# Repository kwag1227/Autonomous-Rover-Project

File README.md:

# Autonomous Rover Project

This repository contains all design files, software, and documentation for an all-terrain, six-legged rover capable of navigating rough terrain and collecting environmental samples. It is a personal robotics project focused on demonstrating skills in embedded systems, motor control, and computer vision.

## 🚀 Project Goals

- Navigate difficult terrain using a rocker-bogie suspension system
- Collect and store small samples (e.g., rocks or soil)
- Avoid untraversable obstacles using sensors
- Showcase design and control of a multi-motor robotic system
- Build a custom PCB
- Implement ROS2 and Gazebo Simulation

## 📁 Repository Structure

- /code                       Microcontroller firmware and Raspberry Pi software  
- /mechanical design          CAD files & mechanical designs
- /electrical schematics      PCB schematics & electrical diagrams
- /vision                     Computer vision and object detection scripts  
- /docs                       Design notes and planning documents 
- /tests                      Testing scripts and logs  
- /media                      Images or videos of the rover in progress
- /references                 Reference images that I gathered from online
- /archives                   Outdated documents/files that are no longer in use
- README.md                   Project overview and documentation  

## 🧰 Technologies Used

- Raspberry Pi 4 (with OpenCV for computer vision)
- Raspberry Pi Pico
- Python Programming Language and ROS
- Rocker-Bogie Suspension System
- Camera Module
- Sensors (IMU, GPS, Encoders, Magnetometer)
- Custom PCB

## 🛠️ Current Progress

- [x] Preliminary Research
- [x] Conceptual Design
- [x] Power Distribution Design
- [x] Control/Communication Design
- [x] Master Electrical Schematic Design
- [x] PCB Design
- [x] CAD Design
- [x] Finalized BOM
- [x] Mechanical Assembly
- [ ] Electrical Assembly
- [ ] Basic Drive Logic
- [ ] Autonomy Logic
- [ ] Articulated Arm Design
- [ ] Articulation Logic 

## 📷 Media

*Add photos or videos here later*

## 🔒 Status

This is a personal project still under development

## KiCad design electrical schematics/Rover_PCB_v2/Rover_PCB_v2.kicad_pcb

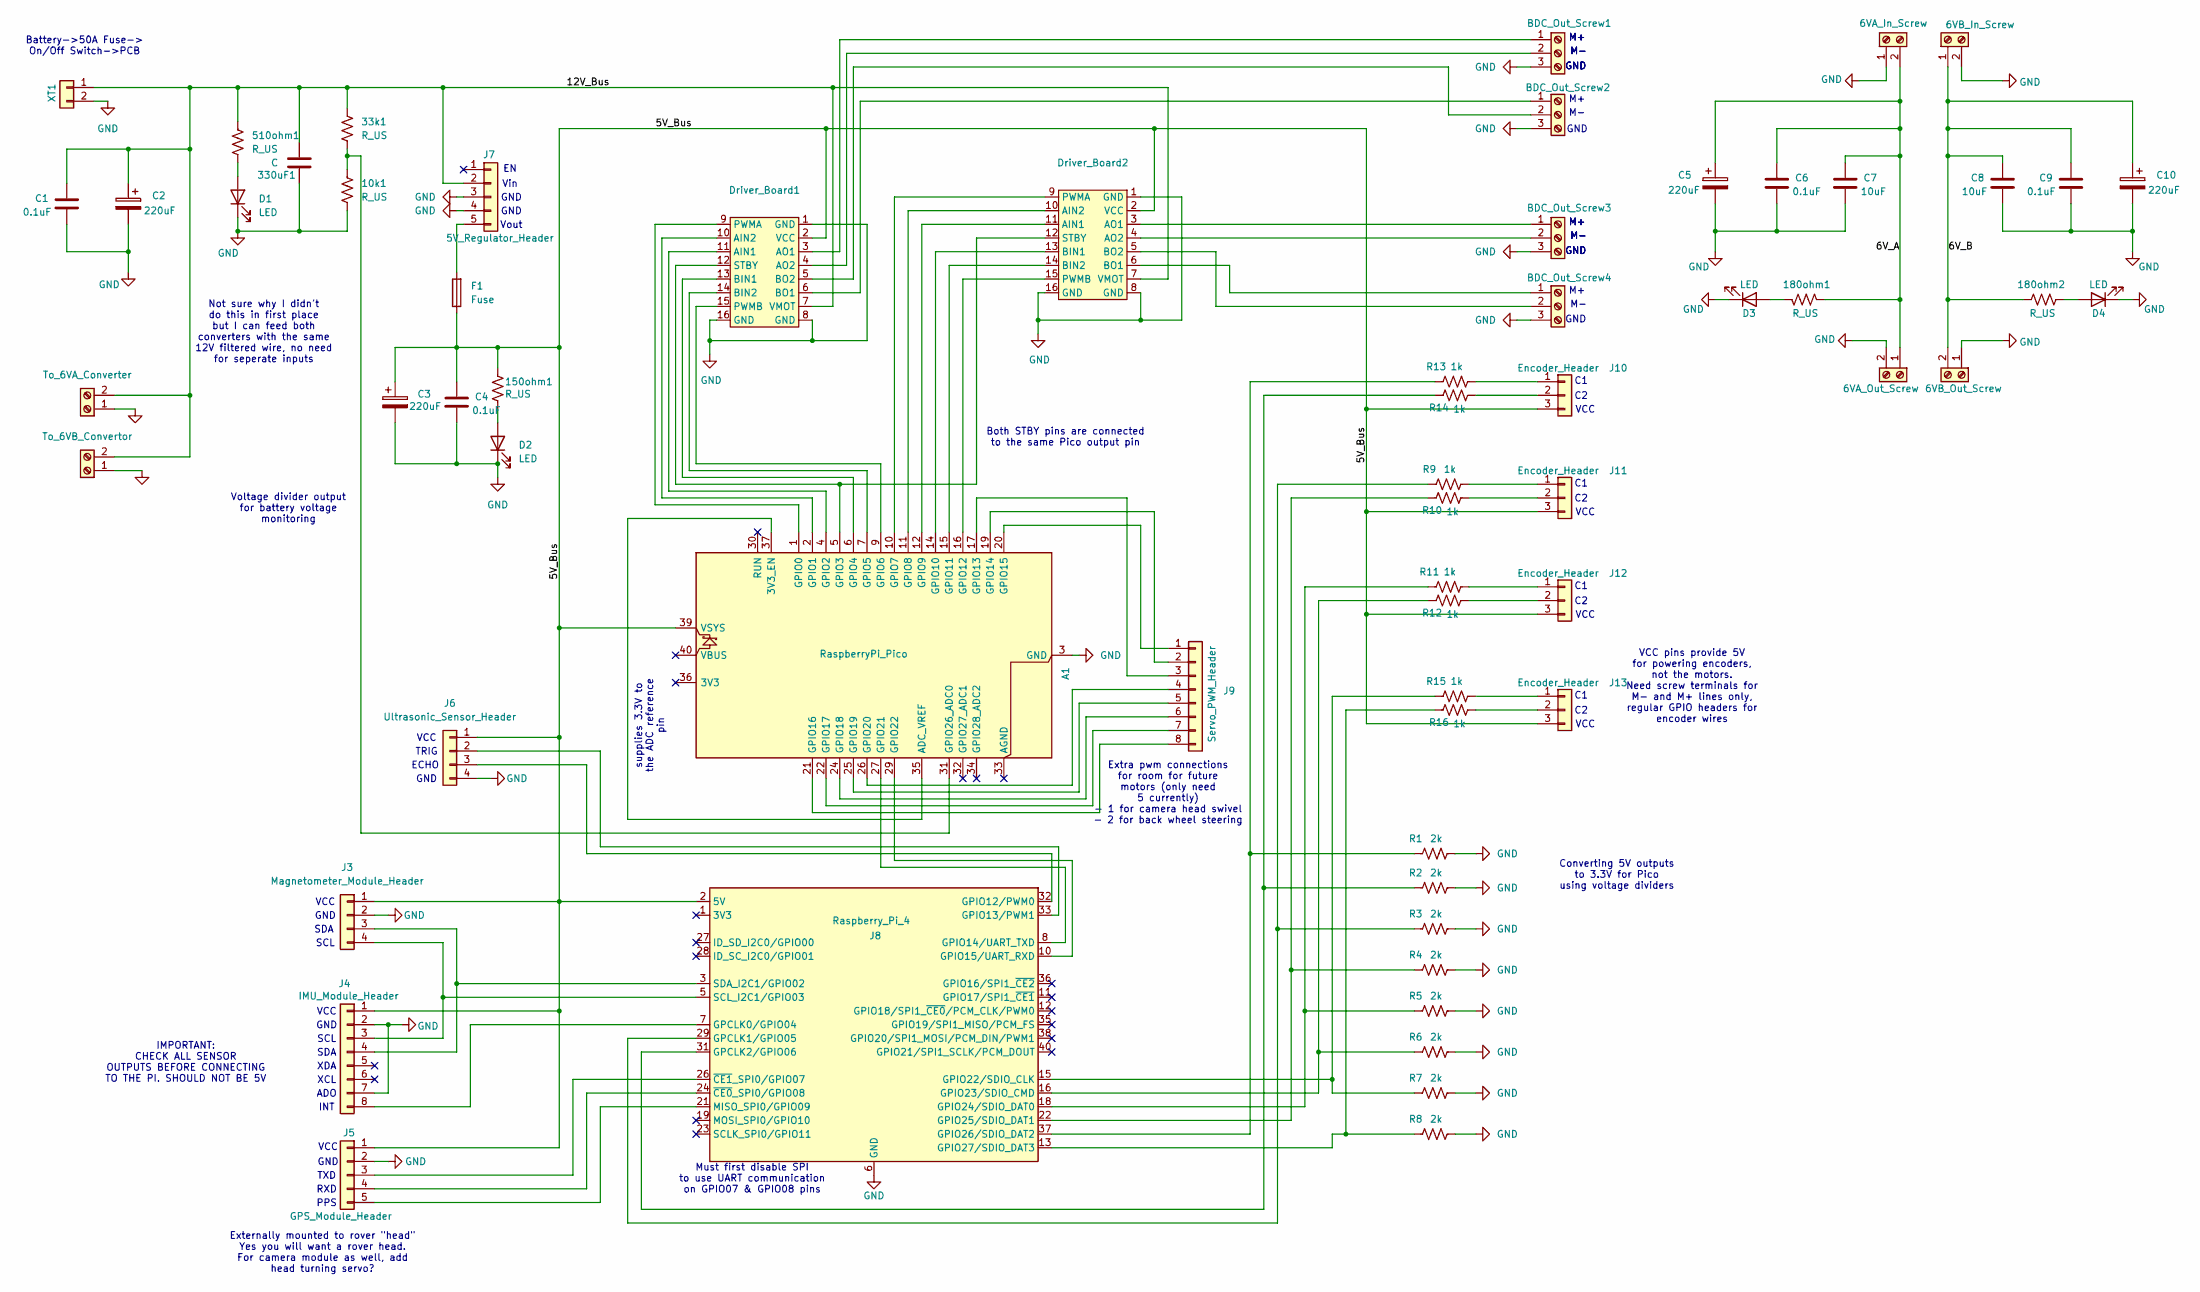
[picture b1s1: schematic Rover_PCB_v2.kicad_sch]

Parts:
10k1, 33k1, 150ohm1, 180ohm1, 180ohm2, 510ohm1: R_US; R_Axial_DIN0207_L6.3mm_D2.5mm_P7.62mm_Horizontal
330uF1: C; CP_Radial_D4.0mm_P2.00mm
A1: RaspberryPi_Pico; RaspberryPi_Pico_Common_Unspecified
BDC_Out_Screw1, BDC_Out_Screw2, BDC_Out_Screw3, BDC_Out_Screw4: BDC_Motor_Screw_Terminal; 01x03_Screw_Terminal
C1, C4, C6, C9: 0.1uF; CP_Radial_D4.0mm_P2.00mm
C2, C3, C5, C10: 220uF; CP_Radial_D6.3mm_P2.50mm
C7, C8: 10uF; CP_Radial_D4.0mm_P2.00mm
D1, D2, D3, D4: LED; LED_D3.0mm
Driver_Board1, Driver_Board2: Motor Driver Board
F1: Fuse; Fuse_TH_5A
J1: To_6VA_Converter; 12AWG Screw Terminal
J2: To_6VB_Convertor; 12AWG Screw Terminal
J3: Magnetometer_Module_Header; PinHeader_1x04_P2.54mm_Vertical
J4: IMU_Module_Header; PinHeader_1x08_P2.54mm_Vertical
J5: GPS_Module_Header; PinHeader_1x05_P2.54mm_Vertical
J6: Ultrasonic_Sensor_Header; PinHeader_1x04_P2.54mm_Vertical
J7: 5V_Regulator_Header; PinHeader_1x05_P2.54mm_Vertical
J8: Raspberry_Pi_4; SULLINS_PPTC202LFBN-RC
J9: Servo_PWM_Header; PinHeader_1x08_P2.54mm_Vertical
J10, J11, J12, J13: Encoder_Header; PinHeader_1x03_P2.54mm_Vertical
J14: 6VA_In_Screw; 12AWG Screw Terminal
J15: 6VA_Out_Screw; 12AWG Screw Terminal
J16: 6VB_In_Screw; 12AWG Screw Terminal
J17: 6VB_Out_Screw; 12AWG Screw Terminal
R1, R2, R3, R4, R5, R6, R7, R8: 2k; R_Axial_DIN0207_L6.3mm_D2.5mm_P7.62mm_Horizontal
R9, R10, R11, R12, R13, R14, R15, R16: 1k; R_Axial_DIN0207_L6.3mm_D2.5mm_P7.62mm_Horizontal
XT1: XT60_Port; AMASS_XT60-F_1x02_P7.20mm_Vertical

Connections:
/5V_Bus: 150ohm1.1, A1.39 (VSYS), C3.1, C4.1, Driver_Board1.2 (VCC), Driver_Board2.2 (VCC), F1.1, J3.1 (VCC), J4.1, J5.1 (VCC), J6.1 (VCC), J8.2 (5V), J8.4 (5V), J10.3 (VCC), J11.3 (VCC), J12.3 (VCC), J13.3 (VCC)
/6V_A: 180ohm1.1, C5.1, C6.1, C7.1, J14.2, J15.1
/6V_B: 180ohm2.1, C8.1, C9.1, C10.1, J16.1, J17.2
/12V_Bus: 33k1.2, 330uF1.1, 510ohm1.1, C1.1, C2.1, Driver_Board1.7 (VMOT), Driver_Board2.7 (VMOT), J1.2, J2.2, J7.2 (Vin), XT1.1 (12V_raw); also elsewhere on the board
GND: 10k1.2, 330uF1.2, A1.3 (GND), A1.8 (GND), A1.13 (GND), A1.18 (GND), A1.23 (GND), A1.28 (GND), A1.38 (GND), BDC_Out_Screw1.3 (GND), BDC_Out_Screw2.3 (GND), BDC_Out_Screw3.3 (GND), BDC_Out_Screw4.3 (GND), C1.2, C2.2, C3.2, C4.2, C5.2, C6.2, C7.2, C8.2, C9.2, C10.2, D1.2 (K), D2.2 (K), D3.2 (K), D4.2 (K), Driver_Board1.1 (GND), Driver_Board1.8 (GND), Driver_Board1.16 (GND), Driver_Board2.1 (GND), Driver_Board2.8 (GND), Driver_Board2.16 (GND), J1.1, J2.1, J3.2 (GND), J4.2, J4.7, J5.2 (GND), J6.4 (GND), J7.3 (GND), J7.4 (GND), J8.6 (GND), J8.9 (GND), J8.14 (GND), J8.20 (GND), J8.25 (GND), J8.30 (GND), J8.34 (GND), J8.39 (GND), J14.1, J15.2, J16.2, J17.1, R1.2, R2.2, R3.2, R4.2, R5.2, R6.2, R7.2, R8.2, XT1.2 (GND); also elsewhere on the board
unnamed: A1.35 (ADC_VREF), A1.37 (3V3_EN)
unnamed: A1.1 (GPIO0), Driver_Board1.9 (PWMA)
unnamed: A1.2 (GPIO1), Driver_Board1.10 (AIN2)
unnamed: A1.4 (GPIO2), Driver_Board1.11 (AIN1)
unnamed: A1.5 (GPIO3), Driver_Board1.12 (STBY), Driver_Board2.12 (STBY)
unnamed: A1.6 (GPIO4), Driver_Board1.13 (BIN1)
unnamed: A1.7 (GPIO5), Driver_Board1.14 (BIN2)
unnamed: A1.9 (GPIO6), Driver_Board1.15 (PWMB)
unnamed: A1.10 (GPIO7), Driver_Board2.9 (PWMA)
unnamed: A1.11 (GPIO8), Driver_Board2.10 (AIN2)
unnamed: A1.12 (GPIO9), Driver_Board2.11 (AIN1)
unnamed: A1.14 (GPIO10), Driver_Board2.13 (BIN1)
unnamed: A1.15 (GPIO11), Driver_Board2.14 (BIN2)
unnamed: A1.16 (GPIO12), Driver_Board2.15 (PWMB)
unnamed: A1.17 (GPIO13), J9.3
unnamed: A1.19 (GPIO14), J9.2
unnamed: A1.20 (GPIO15), J9.1
unnamed: A1.21 (GPIO16), J9.8
unnamed: A1.22 (GPIO17), J9.7
unnamed: A1.24 (GPIO18), J9.6
unnamed: A1.25 (GPIO19), J9.5
unnamed: A1.26 (GPIO20), J9.4
unnamed: A1.27 (GPIO21), J8.8 (GPIO14/UART_TXD)
unnamed: A1.29 (GPIO22), J8.10 (GPIO15/UART_RXD)
unnamed: 10k1.1, 33k1.1, A1.31 (GPIO26_ADC0)
unnamed 30: BDC_Out_Screw1.1 (M+), Driver_Board1.3 (AO1); also elsewhere on the board
unnamed 31: BDC_Out_Screw1.2 (M-), Driver_Board1.4 (AO2); also elsewhere on the board
unnamed: BDC_Out_Screw2.1 (M+), Driver_Board1.6 (BO1)
unnamed: BDC_Out_Screw2.2 (M-), Driver_Board1.5 (BO2)
unnamed: BDC_Out_Screw3.1 (M+), Driver_Board2.3 (AO1)
unnamed: BDC_Out_Screw3.2 (M-), Driver_Board2.4 (AO2)
unnamed: BDC_Out_Screw4.1 (M+), Driver_Board2.6 (BO1)
unnamed: BDC_Out_Screw4.2 (M-), Driver_Board2.5 (BO2)
unnamed: 510ohm1.2, D1.1 (A)
unnamed: 150ohm1.2, D2.1 (A)
unnamed: 180ohm1.2, D3.1 (A)
unnamed: 180ohm2.2, D4.1 (A)
unnamed: J3.4 (SCL), J4.3, J8.5 (SCL_I2C1/GPIO03)
unnamed: J3.3 (SDA), J4.4, J8.3 (SDA_I2C1/GPIO02)
unnamed: J4.8, J8.7 (GPCLK0/GPIO04)
unnamed: J5.5 (PPS), J8.21 (MISO_SPI0/GPIO09)
unnamed: J5.4 (RXD), J8.24 (~CE0_SPI0/GPIO08)
unnamed: J5.3 (TXD), J8.26 (~CE1_SPI0/GPIO07)
unnamed: J6.3 (Echo), J8.32 (GPIO12/PWM0)
unnamed: J6.2 (Trig), J8.33 (GPIO13/PWM1)
unnamed: F1.2, J7.5 (Vout)
unnamed: J8.29 (GPCLK1/GPIO05), R3.1, R9.1
unnamed: J8.31 (GPCLK2/GPIO06), R2.1, R14.1
unnamed: J8.15 (GPIO22/SDIO_CLK), R7.1, R15.1
unnamed: J8.16 (GPIO23/SDIO_CMD), R6.1, R12.1
unnamed: J8.18 (GPIO24/SDIO_DAT0), R5.1, R11.1
unnamed: J8.22 (GPIO25/SDIO_DAT1), R4.1, R10.1
unnamed: J8.37 (GPIO26/SDIO_DAT2), R1.1, R13.1
unnamed: J8.13 (GPIO27/SDIO_DAT3), R8.1, R16.1
unnamed: J10.1 (C1), R13.2
unnamed: J10.2 (C2), R14.2
unnamed: J11.1 (C1), R9.2
unnamed: J11.2 (C2), R10.2
unnamed: J12.1 (C1), R11.2
unnamed: J12.2 (C2), R12.2
unnamed: J13.1 (C1), R15.2
unnamed: J13.2 (C2), R16.2

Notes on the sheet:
GND
INT
Externally mounted to rover "head" Yes you will want a rover head. For camera module as well, add head turning servo?
GND
TRIG
VCC
Vin
SDA
SCL
supplies 3.3V to the ADC reference pin
TXD
Voltage divider output for battery voltage monitoring
XCL
Battery->50A Fuse-> On/Off Switch->PCB
IMPORTANT: CHECK ALL SENSOR OUTPUTS BEFORE CONNECTING TO THE PI. SHOULD NOT BE 5V
RXD
VCC pins provide 5V for powering encoders, not the motors. Need screw terminals for M- and M+ lines only, regular GPIO headers for encoder wires
Vout
ECHO
PPS
Both STBY pins are connected to the same Pico output pin
Not sure why I didn't do this in first place but I can feed both converters with the same 12V filtered wire, no need for seperate inputs
XDA
Must first disable SPI to use UART communication on GPIO07 & GPIO08 pins
Extra pwm connections for room for future motors (only need 5 currently) - 1 for camera head swivel - 2 for back wheel steering
ADO
Converting 5V outputs to 3.3V for Pico using voltage dividers

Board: 2 copper layers, 63 parts (0 on the bottom side), 67 nets, no tracks yet.

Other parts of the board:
BDC_Out_Screw: BDC_Motor_Screw_Terminal; 01x03_Screw_Terminal
XT60: XT60_Port; AMASS_XT60-F_1x02_P7.20mm_Vertical

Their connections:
/12V_Bus: XT60.1 (12V_raw); also elsewhere on the board
GND: BDC_Out_Screw.3 (GND), XT60.2 (GND); also elsewhere on the board
unnamed 30: BDC_Out_Screw.1 (M+); also elsewhere on the board
unnamed 31: BDC_Out_Screw.2 (M-); also elsewhere on the board

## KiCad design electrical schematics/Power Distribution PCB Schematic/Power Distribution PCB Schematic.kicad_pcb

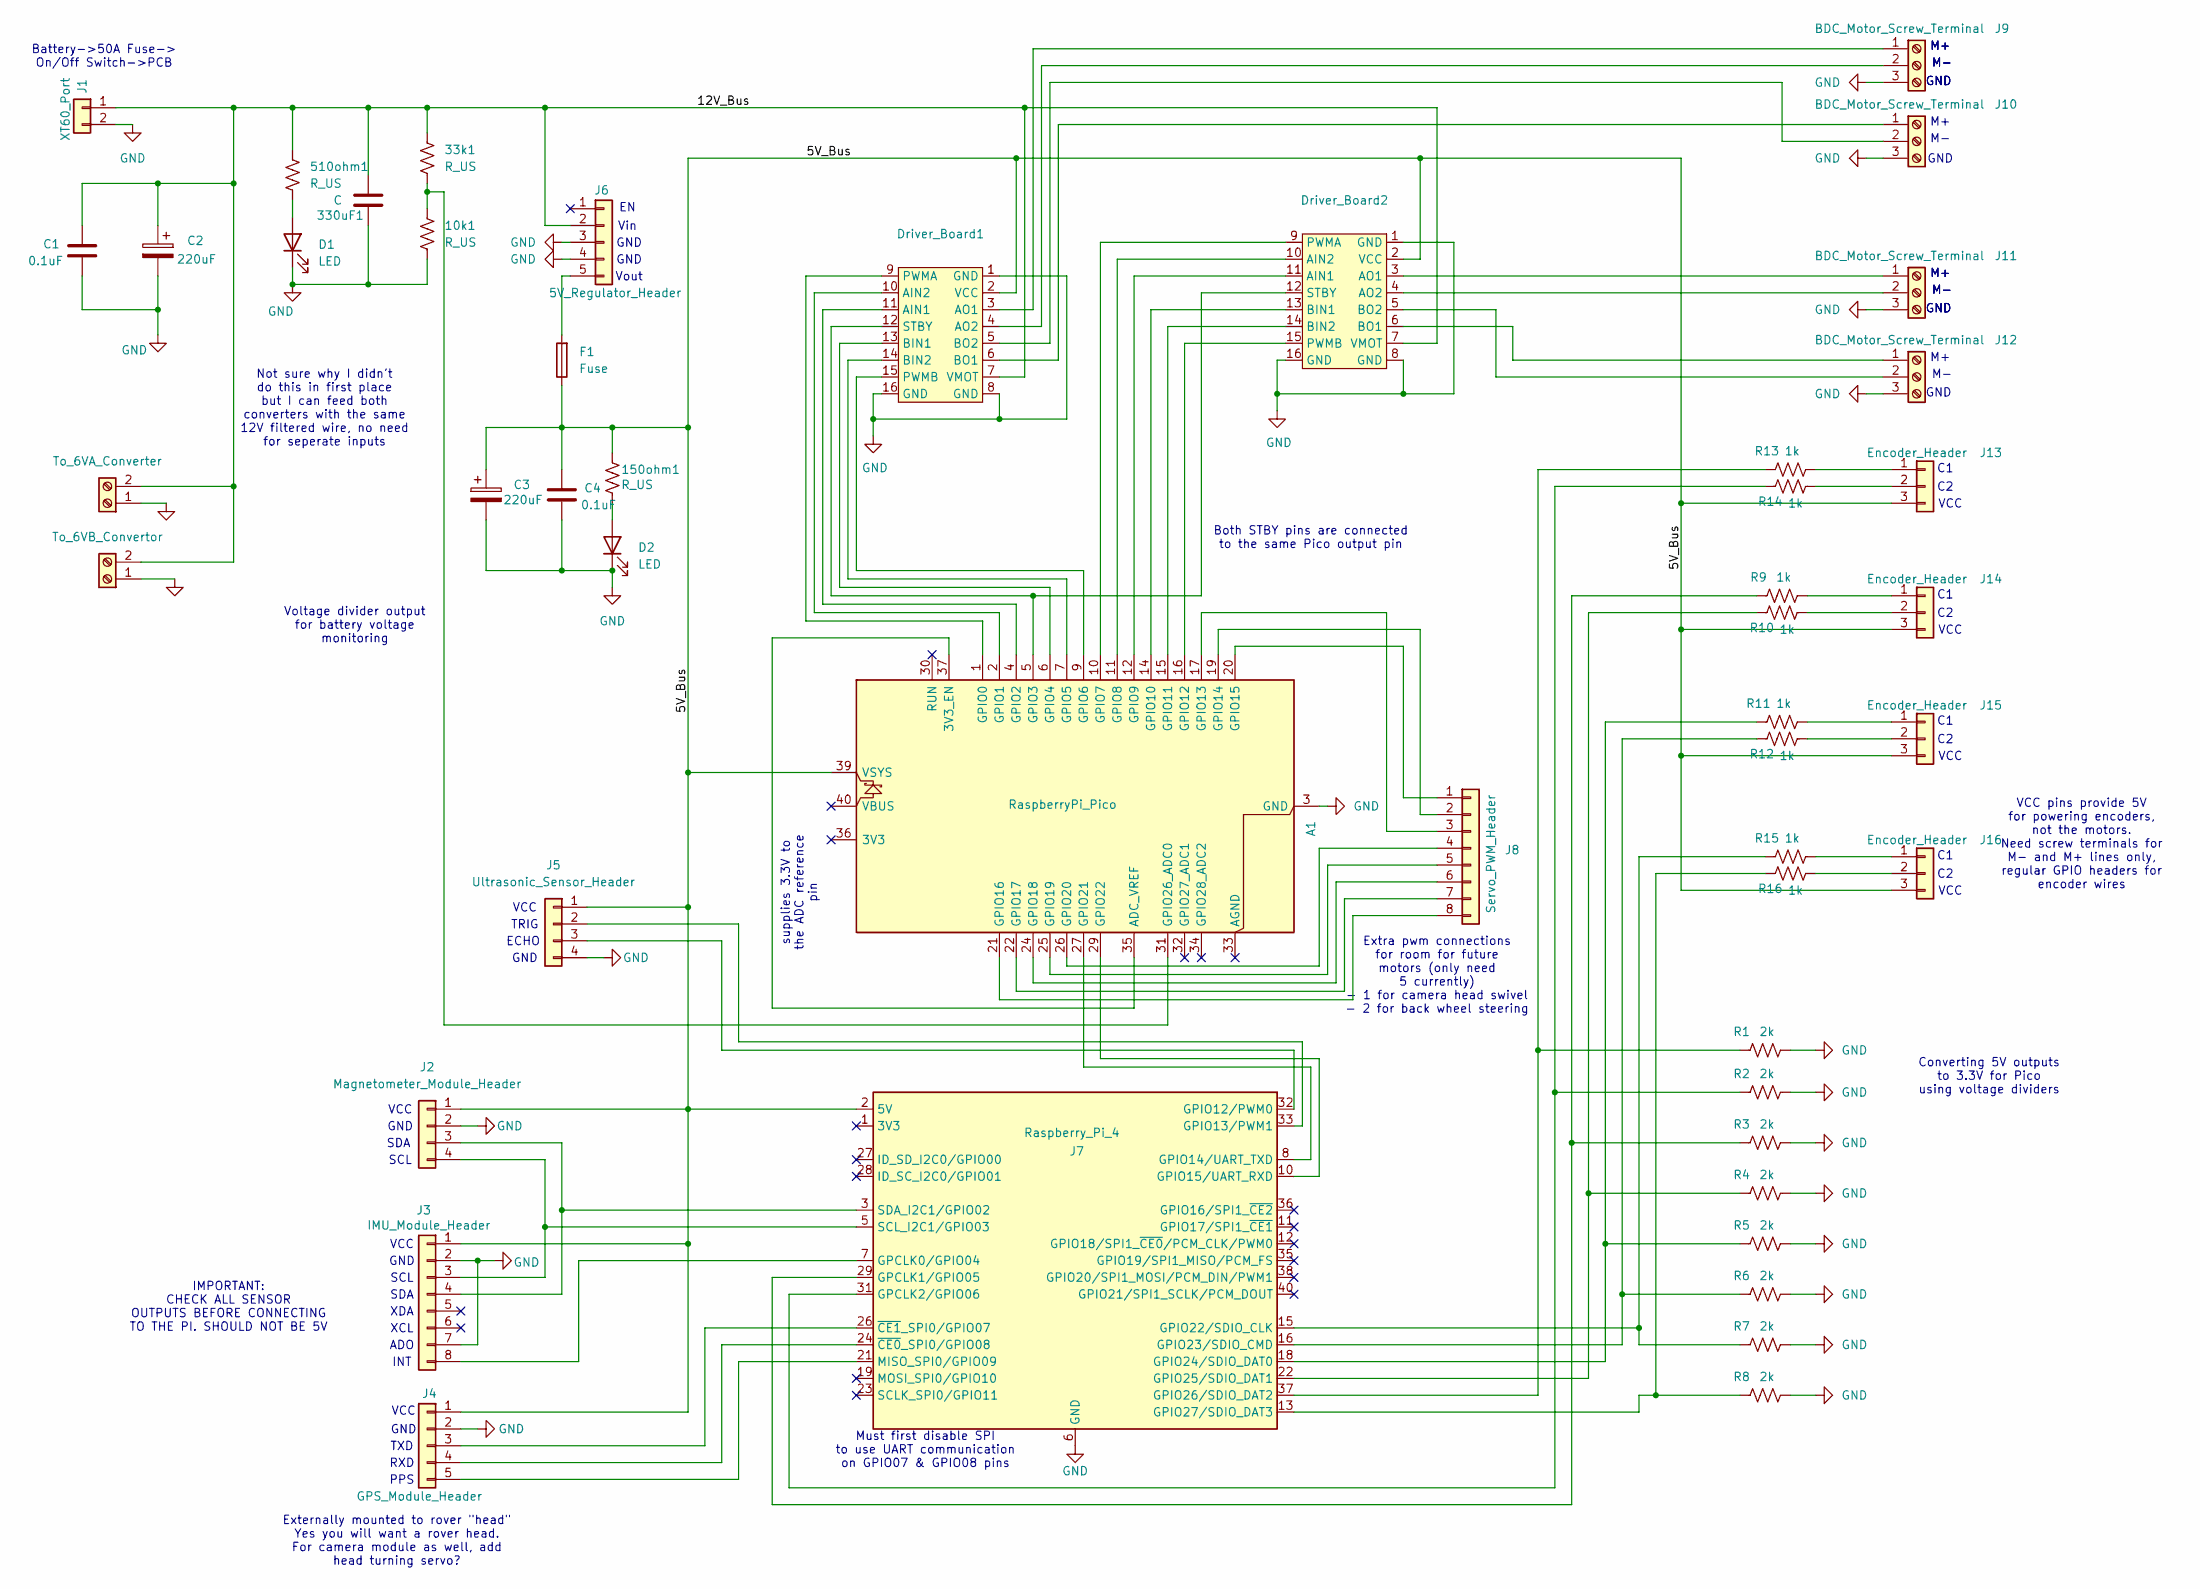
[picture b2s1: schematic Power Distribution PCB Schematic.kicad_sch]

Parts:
10k1, 33k1, 150ohm1, 510ohm1: R_US; R_Axial_DIN0207_L6.3mm_D2.5mm_P7.62mm_Horizontal
330uF1: C; Ceramic Cap
A1: RaspberryPi_Pico; RaspberryPi_Pico_Common_Unspecified
C1, C4: 0.1uF; Ceramic Cap
C2, C3: 220uF; CP_Radial_D6.3mm_P2.50mm
D1, D2: LED; LED_D3.0mm
Driver_Board1, Driver_Board2: Motor Driver Board
F1: Fuse; Fuse_TH_5A
J1: XT60_Port; AMASS_XT60-F_1x02_P7.20mm_Vertical
J2: Magnetometer_Module_Header; PinHeader_1x04_P2.54mm_Vertical
J3: IMU_Module_Header; PinHeader_1x08_P2.54mm_Vertical
J4: GPS_Module_Header; PinHeader_1x05_P2.54mm_Vertical
J5: Ultrasonic_Sensor_Header; PinHeader_1x04_P2.54mm_Vertical
J6: 5V_Regulator_Header; PinHeader_1x05_P2.54mm_Vertical
J7: Raspberry_Pi_4; SULLINS_PPTC202LFBN-RC
J8: Servo_PWM_Header; PinHeader_1x08_P2.54mm_Vertical
J9, J10, J11, J12: BDC_Motor_Screw_Terminal; 01x03_Screw_Terminal
J13, J14, J15, J16: Encoder_Header; PinHeader_1x03_P2.54mm_Vertical
R1, R2, R3, R4, R5, R6, R7, R8: 2k; R_Axial_DIN0207_L6.3mm_D2.5mm_P7.62mm_Horizontal
R9, R10, R11, R12, R13, R14, R15, R16: 1k; R_Axial_DIN0207_L6.3mm_D2.5mm_P7.62mm_Horizontal
To_6VA_Conv1: To_6VA_Converter; 12AWG Screw Terminal
To_6VB_Conv1: To_6VB_Convertor; 12AWG Screw Terminal

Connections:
/5V_Bus: 150ohm1.1, A1.39 (VSYS), C3.1, C4.1, Driver_Board1.2 (VCC), Driver_Board2.2 (VCC), F1.1, J2.1 (VCC), J3.1, J4.1 (VCC), J5.1 (VCC), J7.2 (5V), J7.4 (5V), J13.3 (VCC), J14.3 (VCC), J15.3 (VCC), J16.3 (VCC)
/12V_Bus: 33k1.2, 330uF1.1, 510ohm1.1, C1.1, C2.1, Driver_Board1.7 (VMOT), Driver_Board2.7 (VMOT), J1.1 (12V_raw), J6.2 (Vin), To_6VA_Conv1.2, To_6VB_Conv1.2
GND: 10k1.2, 330uF1.2, A1.3 (GND), A1.8 (GND), A1.13 (GND), A1.18 (GND), A1.23 (GND), A1.28 (GND), A1.38 (GND), C1.2, C2.2, C3.2, C4.2, D1.2 (K), D2.2 (K), Driver_Board1.1 (GND), Driver_Board1.8 (GND), Driver_Board1.16 (GND), Driver_Board2.1 (GND), Driver_Board2.8 (GND), Driver_Board2.16 (GND), J1.2 (GND), J2.2 (GND), J3.2, J3.7, J4.2 (GND), J5.4 (GND), J6.3 (GND), J6.4 (GND), J7.6 (GND), J7.9 (GND), J7.14 (GND), J7.20 (GND), J7.25 (GND), J7.30 (GND), J7.34 (GND), J7.39 (GND), J9.3 (GND), J10.3 (GND), J11.3 (GND), J12.3 (GND), R1.2, R2.2, R3.2, R4.2, R5.2, R6.2, R7.2, R8.2, To_6VA_Conv1.1, To_6VB_Conv1.1
unnamed: A1.35 (ADC_VREF), A1.37 (3V3_EN)
unnamed: A1.1 (GPIO0), Driver_Board1.9 (PWMA)
unnamed: A1.2 (GPIO1), Driver_Board1.10 (AIN2)
unnamed: A1.4 (GPIO2), Driver_Board1.11 (AIN1)
unnamed: A1.5 (GPIO3), Driver_Board1.12 (STBY), Driver_Board2.12 (STBY)
unnamed: A1.6 (GPIO4), Driver_Board1.13 (BIN1)
unnamed: A1.7 (GPIO5), Driver_Board1.14 (BIN2)
unnamed: A1.9 (GPIO6), Driver_Board1.15 (PWMB)
unnamed: A1.10 (GPIO7), Driver_Board2.9 (PWMA)
unnamed: A1.11 (GPIO8), Driver_Board2.10 (AIN2)
unnamed: A1.12 (GPIO9), Driver_Board2.11 (AIN1)
unnamed: A1.14 (GPIO10), Driver_Board2.13 (BIN1)
unnamed: A1.15 (GPIO11), Driver_Board2.14 (BIN2)
unnamed: A1.16 (GPIO12), Driver_Board2.15 (PWMB)
unnamed: A1.17 (GPIO13), J8.3
unnamed: A1.19 (GPIO14), J8.2
unnamed: A1.20 (GPIO15), J8.1
unnamed: A1.21 (GPIO16), J8.8
unnamed: A1.22 (GPIO17), J8.7
unnamed: A1.24 (GPIO18), J8.6
unnamed: A1.25 (GPIO19), J8.5
unnamed: A1.26 (GPIO20), J8.4
unnamed: A1.27 (GPIO21), J7.8 (GPIO14/UART_TXD)
unnamed: A1.29 (GPIO22), J7.10 (GPIO15/UART_RXD)
unnamed: 10k1.1, 33k1.1, A1.31 (GPIO26_ADC0)
unnamed: 510ohm1.2, D1.1 (A)
unnamed: 150ohm1.2, D2.1 (A)
unnamed: Driver_Board1.3 (AO1), J9.1 (M+)
unnamed: Driver_Board1.4 (AO2), J9.2 (M-)
unnamed: Driver_Board1.6 (BO1), J10.1 (M+)
unnamed: Driver_Board1.5 (BO2), J10.2 (M-)
unnamed: Driver_Board2.3 (AO1), J11.1 (M+)
unnamed: Driver_Board2.4 (AO2), J11.2 (M-)
unnamed: Driver_Board2.6 (BO1), J12.1 (M+)
unnamed: Driver_Board2.5 (BO2), J12.2 (M-)
unnamed: J2.4 (SCL), J3.3, J7.5 (SCL_I2C1/GPIO03)
unnamed: J2.3 (SDA), J3.4, J7.3 (SDA_I2C1/GPIO02)
unnamed: J3.8, J7.7 (GPCLK0/GPIO04)
unnamed: J4.5 (PPS), J7.21 (MISO_SPI0/GPIO09)
unnamed: J4.4 (RXD), J7.24 (~CE0_SPI0/GPIO08)
unnamed: J4.3 (TXD), J7.26 (~CE1_SPI0/GPIO07)
unnamed: J5.3 (Echo), J7.32 (GPIO12/PWM0)
unnamed: J5.2 (Trig), J7.33 (GPIO13/PWM1)
unnamed: F1.2, J6.5 (Vout)
unnamed: J7.29 (GPCLK1/GPIO05), R3.1, R9.1
unnamed: J7.31 (GPCLK2/GPIO06), R2.1, R14.1
unnamed: J7.15 (GPIO22/SDIO_CLK), R7.1, R15.1
unnamed: J7.16 (GPIO23/SDIO_CMD), R6.1, R12.1
unnamed: J7.18 (GPIO24/SDIO_DAT0), R5.1, R11.1
unnamed: J7.22 (GPIO25/SDIO_DAT1), R4.1, R10.1
unnamed: J7.37 (GPIO26/SDIO_DAT2), R1.1, R13.1
unnamed: J7.13 (GPIO27/SDIO_DAT3), R8.1, R16.1
unnamed: J13.1 (C1), R13.2
unnamed: J13.2 (C2), R14.2
unnamed: J14.1 (C1), R9.2
unnamed: J14.2 (C2), R10.2
unnamed: J15.1 (C1), R11.2
unnamed: J15.2 (C2), R12.2
unnamed: J16.1 (C1), R15.2
unnamed: J16.2 (C2), R16.2

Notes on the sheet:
GND
INT
Externally mounted to rover "head" Yes you will want a rover head. For camera module as well, add head turning servo?
GND
TRIG
VCC
Vin
SDA
SCL
supplies 3.3V to the ADC reference pin
TXD
Voltage divider output for battery voltage monitoring
XCL
Battery->50A Fuse-> On/Off Switch->PCB
IMPORTANT: CHECK ALL SENSOR OUTPUTS BEFORE CONNECTING TO THE PI. SHOULD NOT BE 5V
RXD
VCC pins provide 5V for powering encoders, not the motors. Need screw terminals for M- and M+ lines only, regular GPIO headers for encoder wires
Vout
ECHO
PPS
Both STBY pins are connected to the same Pico output pin
Not sure why I didn't do this in first place but I can feed both converters with the same 12V filtered wire, no need for seperate inputs
XDA
Must first disable SPI to use UART communication on GPIO07 & GPIO08 pins
Extra pwm connections for room for future motors (only need 5 currently) - 1 for camera head swivel - 2 for back wheel steering
ADO
Converting 5V outputs to 3.3V for Pico using voltage dividers

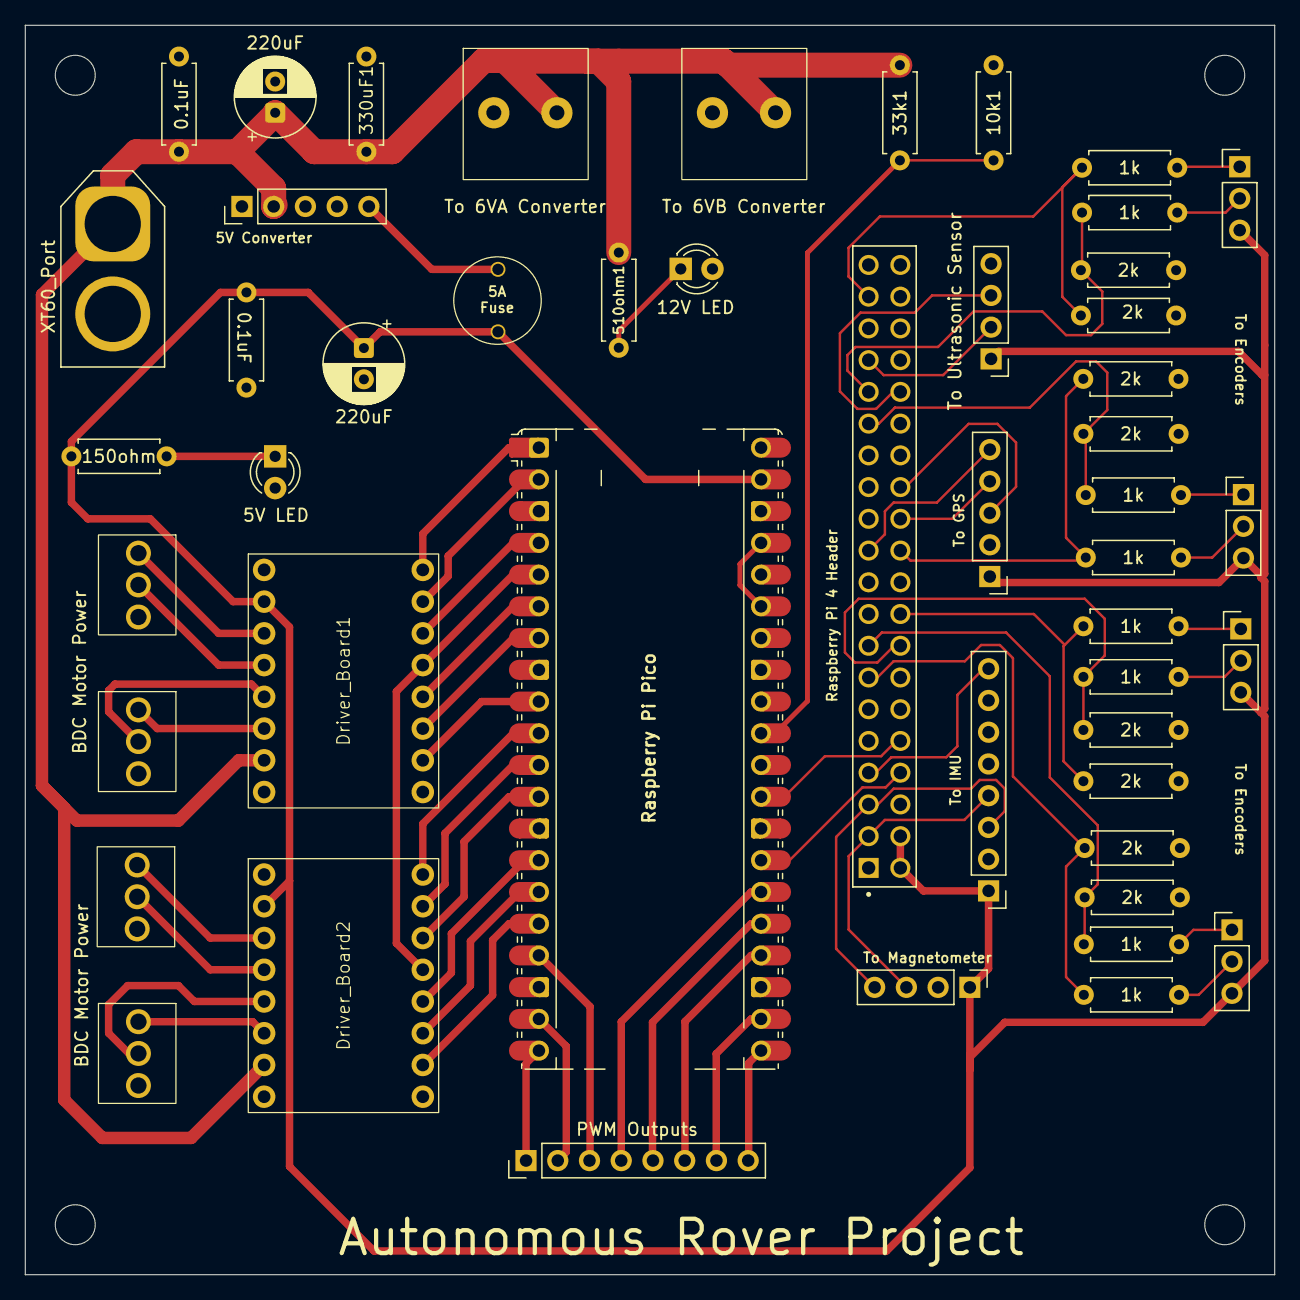
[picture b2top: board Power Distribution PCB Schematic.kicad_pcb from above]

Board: 2 copper layers, 100.0 x 100.0 mm, 49 parts (0 on the bottom side), 63 nets.

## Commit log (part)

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2025-05-20 Update README.md
    Adding project info to readme file
2025-05-21 Create rocker_bogie_research.md
    Self-explanatory
2025-05-21 Uploading project overview doc
2025-05-21 Rename Rover Project Overview.docx to docs/project_overview.docx
2025-05-21 Deleted trash file
2025-05-21 Add rocker-bogie notes and reference images
2025-05-21 updating references folder
2025-05-21 Splitting overview doc to markdown files
2025-05-21 Uploading high-level system diagram
2025-05-21 Adding diagram as separate doc
2025-05-22 Adding main project info docs to root folder
2025-05-30 Added performance constraints
2025-05-30 More updates to performnce section
2025-05-30 Adding names to reference images
    Just for improved accessibility and navigation of references folder.
2025-05-30 Adding master sketch file
2025-05-30 Created master sketch
2025-05-30 Slight changes to performance constraints
2025-05-30 Including ROS in timeline
2025-05-30 Update README.md
    Fixing some incorrect info and making slight adjustments
2025-05-30 Rename block_diagram.md to block_diagram_breakdown.md
2025-05-30 Updating Detailed Block Diagrams
2025-05-30 Update to Diagram
2025-06-02 Updating Detailed Block Diagrams
    More accurate description of what is on control PCB board. Also made changes to the roles of the Pi 3 vs Pico. Pico now controls all motor signals and encoder feedback while Pi 3 handles sensor data 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
2025-06-02 Update High-Level Autonomy Block Diagram.png
    Added block relationships and continuous functions block
2025-06-04 Adding master sketch previews to design folder
    Provides easier access to dimensions for referencing.
2025-06-04 Update system block diagrams
    Servos are 5V not 7.4V, will be powered on power distribution PCB 5V bus (high current). Sensors will be powered on control PCB 5V bus (low current).
2025-06-16 idk?
2025-06-17 Power PCB Circuit Schematic
2025-06-17 Add visible schematic
2025-06-17 Updates to power electrical schematic
2025-06-18 Schematic Work
2025-06-20 Finishing schematics
    Block diagrams are slightly outdated- use schematics instead. (Just need to add 3.3V bus to control pcb + its buck converter and filters.
2025-06-25 Updates to schematics/block diagrams
    Removed 3.3V bus. Added LED resistor values. Removed redundant fuse after 12V-6V converter.
2025-06-25 Organizational changes
2025-07-10 Reorganizing
    Mostly electrical file stuff
2025-07-10 Small changes to electrical schematic
2025-07-16 PCB Layout and Schematic Finalization
2025-07-18 Continued chassis work
2025-07-21 Electrical System Modifications
    Forgot about the ultrasonic sensor, added to PCB schematic + layout
2025-07-29 Mechanical Designing
    Finished chassis and began drivetrain
2025-07-29 Continued work
    Completely had to reverse the majority of panels because I realized that the differential is supposed to be seated further back on the rover, not towards the front. (I initially messed up the chassis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
2025-07-29 Drivetrain work
2025-07-30 Drivetrain progress
2025-08-01 Mechanical work
2025-08-01 Continued design
2025-08-05 PCB Layout Adjustments + Drivetrain Design
2025-08-05 Update PCB layout SS
2025-08-06 Drivetrain wheel alignment
2025-08-06 Middle Wheel Joint Design + Realignment
2025-08-07 Top Level Assembly
2025-08-07 Wheel tread adjustment
2025-08-08 Test Script for Pi 4
2025-08-11 CAD Finalization
2025-08-13 learning
2025-08-13 more cpp learning
2025-09-27 Print File Creation
2025-10-08 PCB Schematic v2
2025-10-08 Schematic SS updating
